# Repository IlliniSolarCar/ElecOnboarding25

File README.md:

# ElecOnboarding26
This is used for Electrical Onboarding for the Fall 2026 Semester

We are very excited to get to work with you guys!

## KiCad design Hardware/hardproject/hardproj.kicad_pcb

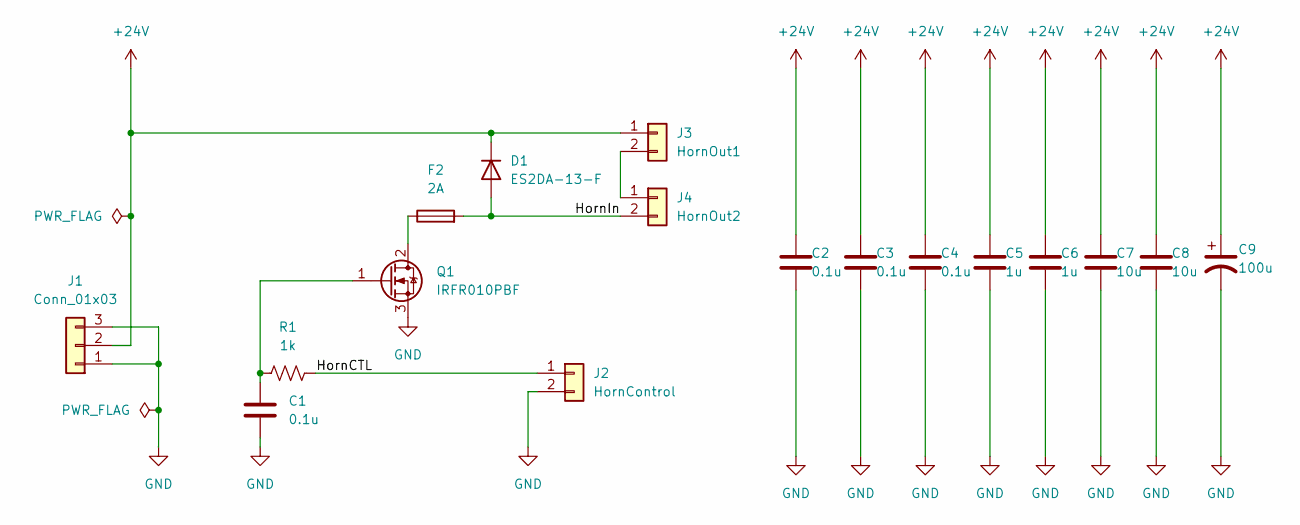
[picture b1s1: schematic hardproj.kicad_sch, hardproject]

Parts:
C1, C2, C3, C4: 0.1u; C_0603_1608Metric_Pad1.08x0.95mm_HandSolder
C5, C6: 1u; C_0603_1608Metric_Pad1.08x0.95mm_HandSolder
C7, C8: 10u; C_0603_1608Metric_Pad1.08x0.95mm_HandSolder
C9: 100u; C_Radial_D8.0mm_H11.5mm_P3.50mm
D1: ES2DA-13-F; D_SMA; MPN ES2DA-13-F
F2: 2A; Fuse_0603_1608Metric_Pad1.05x0.95mm_HandSolder
J1: Conn_01x03; Molex_KK-254_AE-6410-03A_1x03_P2.54mm_Vertical; MPN 022272021
J2: HornControl; Molex_KK-254_AE-6410-02A_1x02_P2.54mm_Vertical; MPN 0022272021
J3: HornOut1; Molex_KK-254_AE-6410-02A_1x02_P2.54mm_Vertical; MPN 0022272021
J4: HornOut2; Molex_KK-254_AE-6410-02A_1x02_P2.54mm_Vertical; MPN 0022272021
Q1: IRFR010PBF; TO-252-2; MPN IRFR010PBF
R1: 1k; R_0603_1608Metric_Pad0.98x0.95mm_HandSolder

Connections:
+24V: C2.1, C3.1, C4.1, C5.1, C6.1, C7.1, C8.1, C9.1, D1.1 (K), J1.2, J3.1
/HornCTL: J2.1, R1.2
/HornIn: D1.2 (A), F2.2, J4.2
GND: C1.2, C2.2, C3.2, C4.2, C5.2, C6.2, C7.2, C8.2, C9.2, J1.1, J1.3, J2.2, Q1.3 (S)
unnamed: J3.2, J4.1
unnamed: F2.1, Q1.2 (D)
unnamed: C1.1, Q1.1 (G), R1.1

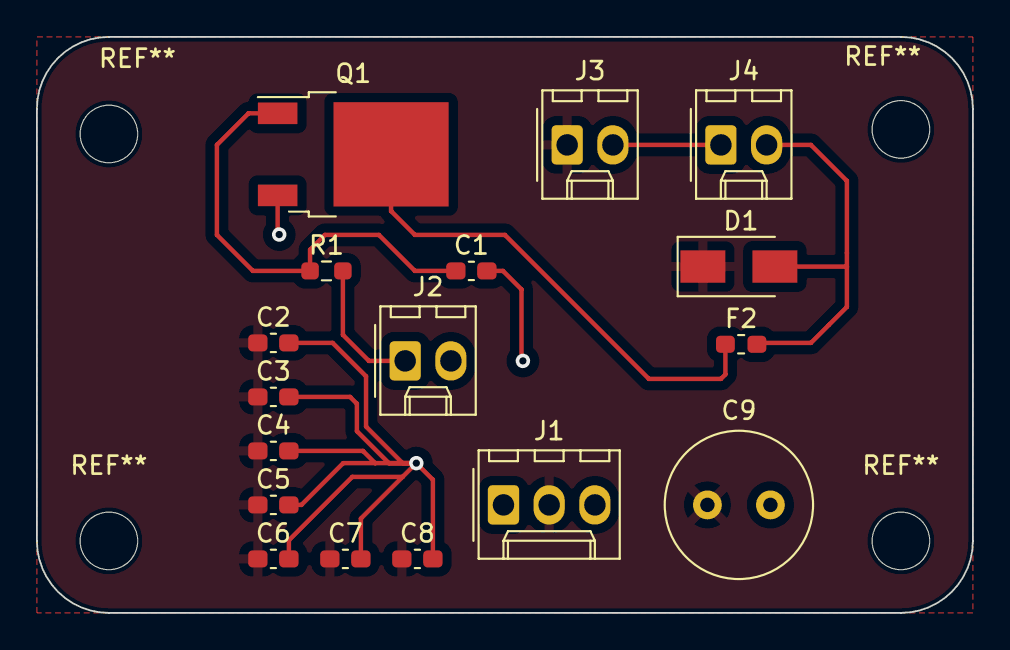
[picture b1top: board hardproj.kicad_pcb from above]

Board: 2 copper layers, 52.0 x 32.0 mm, 17 parts (0 on the bottom side), 7 nets.

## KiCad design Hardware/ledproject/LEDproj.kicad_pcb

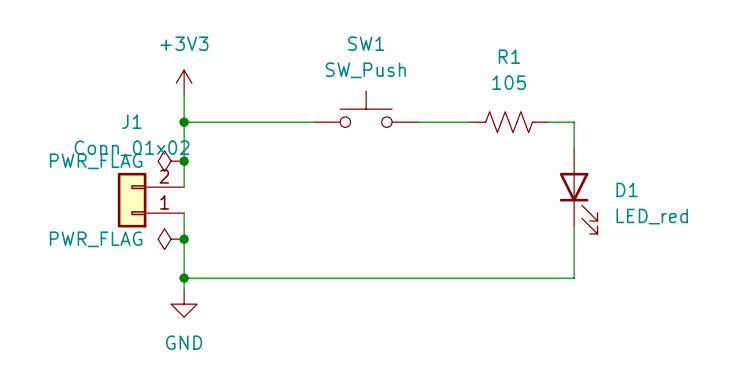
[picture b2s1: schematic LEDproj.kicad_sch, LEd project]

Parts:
D1: LED_red; LED_0603_Symbol_on_F.SilkS
J1: Conn_01x02; Molex_KK-254_AE-6410-02A_1x02_P2.54mm_Vertical; MPN 022272021
R1: 105; R_0603_1608Metric_Pad0.98x0.95mm_HandSolder
SW1: SW_Push; SW_DIP_SPSTx01_Slide_6.7x4.1mm_W8.61mm_P2.54mm_LowProfile; MPN 1825910-6

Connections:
+3V3: J1.2, SW1.1
GND: D1.1 (K), J1.1
unnamed: D1.2 (A), R1.1
unnamed: R1.2, SW1.2

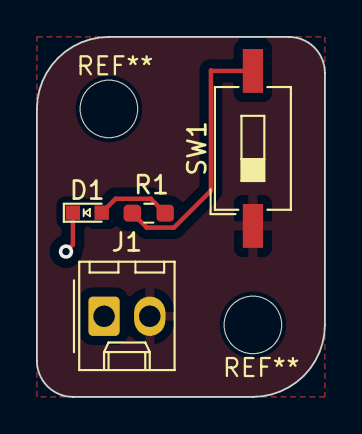
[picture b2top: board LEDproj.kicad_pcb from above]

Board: 2 copper layers, 16.0 x 20.0 mm, 4 parts (0 on the bottom side), 4 nets.

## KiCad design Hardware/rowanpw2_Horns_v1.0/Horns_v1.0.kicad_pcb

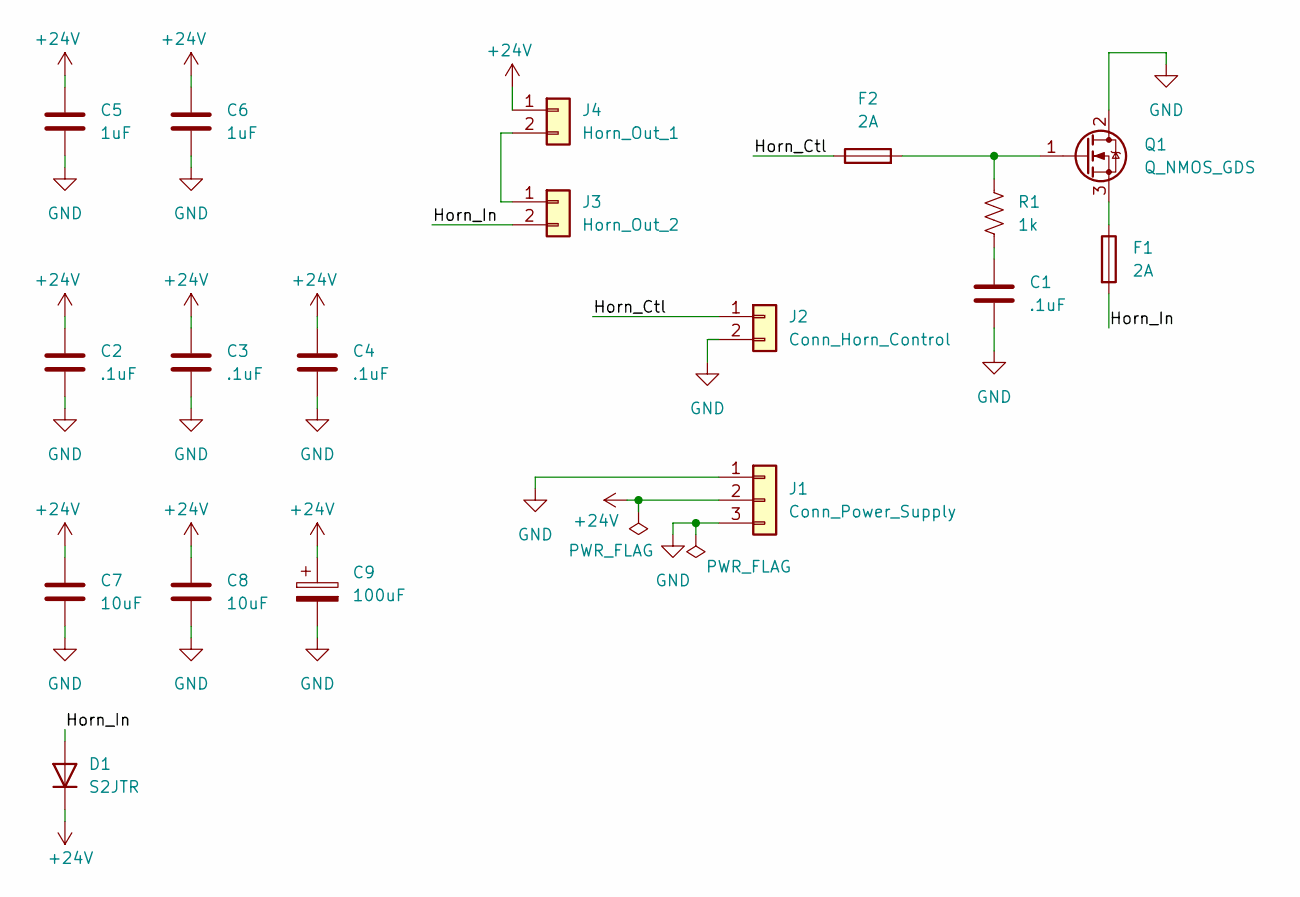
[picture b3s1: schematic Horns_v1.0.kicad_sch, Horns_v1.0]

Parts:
C1, C2, C3, C4: .1uF; C_0603_1608Metric_Pad1.08x0.95mm_HandSolder
C5, C6: 1uF; C_0603_1608Metric_Pad1.08x0.95mm_HandSolder
C7, C8: 10uF; C_0603_1608Metric_Pad1.08x0.95mm_HandSolder
C9: 100uF; CP_Elec_8x10; MPN UCM1A102MNS1GS
D1: S2JTR; D_SMB; MPN S2JTR
F1, F2: 2A; Fuse_1206_3216Metric_Pad1.42x1.75mm_HandSolder
J1: Conn_Power_Supply; Molex_KK-254_AE-6410-03A_1x03_P2.54mm_Vertical; MPN 0022272031
J2: Conn_Horn_Control; Molex_KK-254_AE-6410-02A_1x02_P2.54mm_Vertical; MPN 0022272021
J3: Horn_Out_2; Molex_KK-254_AE-6410-02A_1x02_P2.54mm_Vertical; MPN 0022272021
J4: Horn_Out_1; Molex_KK-254_AE-6410-02A_1x02_P2.54mm_Vertical; MPN 0022272021
Q1: Q_NMOS_GDS; TO-252-2; MPN AUIRF4905S
R1: 1k; R_0603_1608Metric_Pad0.98x0.95mm_HandSolder

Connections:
+24V: C2.1, C3.1, C4.1, C5.1, C6.1, C7.1, C8.1, C9.1, D1.1 (K), J1.2, J4.1
/Horn_Ctl: F2.1, J2.1
/Horn_In: D1.2 (A), F1.2, J3.2
GND: C1.2, C2.2, C3.2, C4.2, C5.2, C6.2, C7.2, C8.2, C9.2, J1.1, J1.3, J2.2, Q1.2 (D)
unnamed: C1.1, R1.2
unnamed: J3.1, J4.2
unnamed: F2.2, Q1.1 (G), R1.1
unnamed: F1.1, Q1.3 (S)

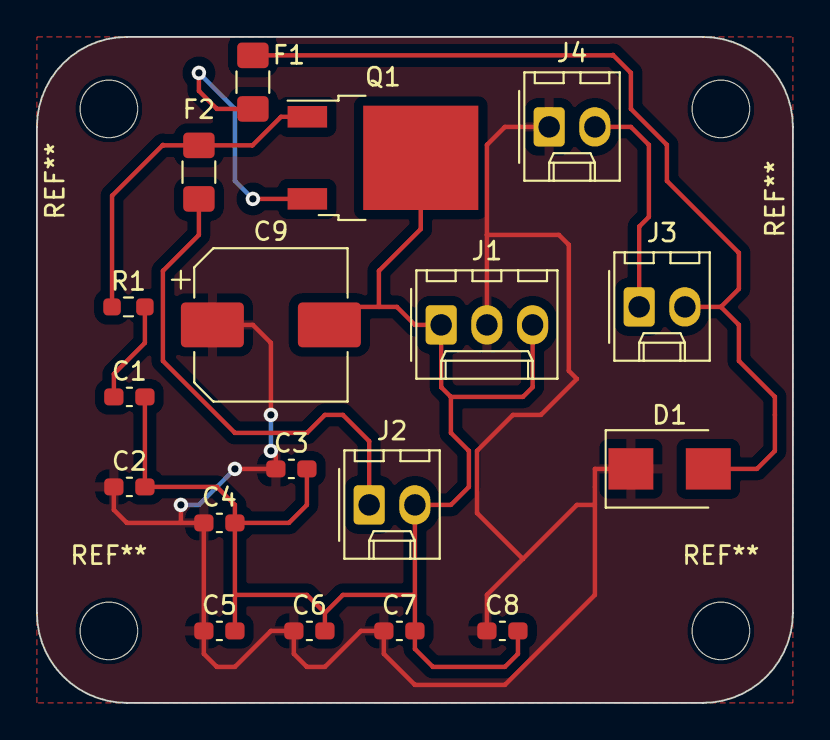
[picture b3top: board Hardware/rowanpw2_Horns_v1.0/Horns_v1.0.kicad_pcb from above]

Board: 2 copper layers, 42.0 x 37.0 mm, 18 parts (0 on the bottom side), 8 nets.

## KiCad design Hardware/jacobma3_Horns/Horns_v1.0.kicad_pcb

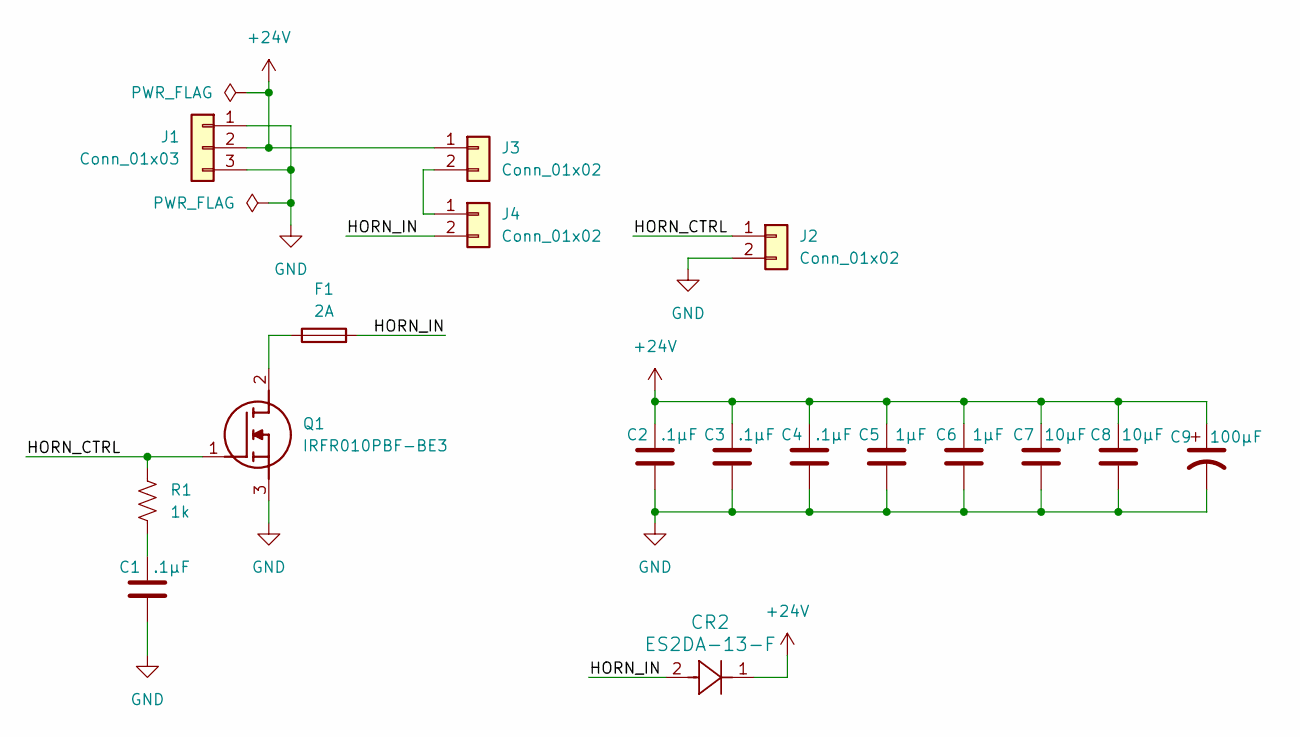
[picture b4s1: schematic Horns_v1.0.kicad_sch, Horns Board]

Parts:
C1, C2, C3, C4: .1μF; C_0603_1608Metric_Pad1.08x0.95mm_HandSolder
C5, C6: 1μF; C_0603_1608Metric_Pad1.08x0.95mm_HandSolder
C7, C8: 10μF; C_0603_1608Metric_Pad1.08x0.95mm_HandSolder
C9: 100μF; C_0603_1608Metric_Pad1.08x0.95mm_HandSolder
CR2: ES2DA-13-F; CR_SMA_DIO
F1: 2A; Fuse_0603_1608Metric_Pad1.05x0.95mm_HandSolder
J1: Conn_01x03; Molex_CLIK-Mate_502382-0370_1x03-1MP_P1.25mm_Vertical
J2, J3, J4: Conn_01x02; Molex_CLIK-Mate_502382-0270_1x02-1MP_P1.25mm_Vertical
Q1: IRFR010PBF-BE3; SQD30N0520L_GE3; Manufacturer_Part_Number IRFR010PBF-BE3; Mouser Part Number 78-IRFR010PBF-BE3
R1: 1k; R_0402_1005Metric_Pad0.72x0.64mm_HandSolder

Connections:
+24V: C2.2, C3.2, C4.2, C5.2, C6.2, C7.2, C8.2, C9.1, CR2.1, J1.2, J3.1
/HORN_CTRL: J2.1, Q1.1 (G), R1.2
/HORN_IN: CR2.2, F1.2, J4.2
GND: C1.1, C2.1, C3.1, C4.1, C5.1, C6.1, C7.1, C8.1, C9.2, J1.1, J1.3, J2.2, Q1.3 (S)
unnamed: C1.2, R1.1
unnamed: J3.2, J4.1
unnamed: F1.1, Q1.2 (D)

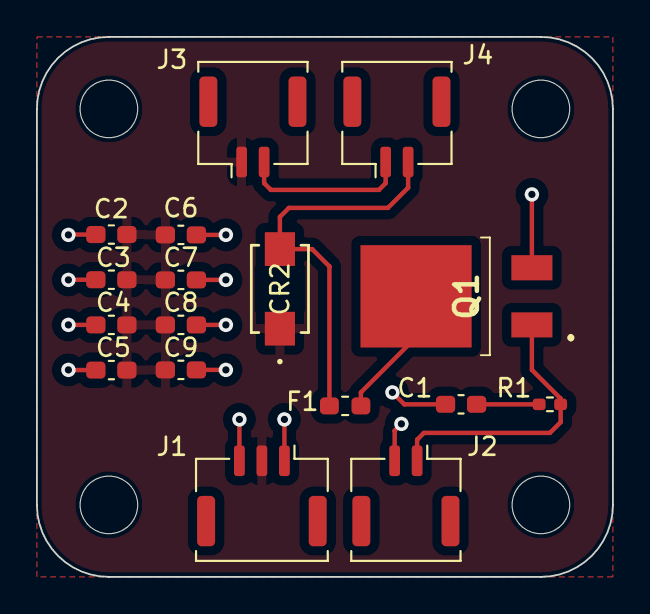
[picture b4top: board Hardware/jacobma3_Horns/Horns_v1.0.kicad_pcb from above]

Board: 2 copper layers, 32.0 x 30.0 mm, 17 parts (0 on the bottom side), 7 nets.

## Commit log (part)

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2025-09-19 Finished Horns Board Layout
    Fixed half-first order RC filter on MOSFET, finished PCB layout. Ran DRC with no errors.
2025-09-19 Finished hardware project 1
2025-09-19 Hardware project1 led pushbutton
2025-09-19 prog1
2025-09-19 Finished LED board schematic and PCB layout
2025-09-19 LED project
2025-09-19 easy projects done
2025-09-19 PCB Layout for Horn Breakout Board Done.
    Created the PCB for the Horn Breakout Board.
2025-09-19 Finished Hard Software Project
    Finished hard software project with potentiometer and LED. Added two lines of code.
2025-09-19 Specs
2025-09-19 firmware project 1 and project 2
2025-09-19 Schematic Horns
2025-09-19 Onboarding Horns Board PCB design
2025-09-19 Gerber files
2025-09-19 Finsihed Schematic for Horn
2025-09-19 Schematic changes
2025-09-20 Spec Sheet
2025-09-20 neha C++ project complete
2025-09-22 horns schematic complete (footprints incomplete)
2025-09-22 finished horns
2025-09-22 Proj 1 done
2025-09-22 blink
2025-09-22 Project 2: Potentiometer Blink Rate
    Finished Project 2 of Firmware and fixed an issue from project 1 of not setting a particular LED high/low
2025-09-23 hengrun2 onboarding project update 2025.9.22 20:46
2025-09-23 hengrun2 onboarding project 2025.9.22 23:03
2025-09-23 Onboarding Project 1 has been completed
2025-09-23 completed firmware proj1 LED
2025-09-23 heartbeat project submission
2025-09-24 Done with firmware?
2025-09-24 projectOneLEDThing
2025-09-24 Finshed Horn onboarding project all flags resolved
2025-09-24 Horns schematic
2025-09-24 Firmware project 1 done
2025-09-24 Project?
2025-09-24 neha horns schematic complete
2025-09-25 horns pcb
2025-09-25 firmware/hardware mini projects done
2025-09-25 Onboarding Hardware Project 1
2025-09-25 onboarding project 1's
2025-09-25 [finished basic hardware project]
2025-09-25 Hardware Project Finished
2025-09-25 Potentiometer Blink Rate Project
2025-09-25 schematic project 1
2025-09-25 finished LED Project
2025-09-25 Finished Schematic
2025-09-25 Working on pcb
2025-09-25 working on layout
2025-09-26 please
2025-09-26 Onboarding Basic Projects
2025-09-26 firmware projects
2025-09-26 Horns Spec Sheet
2025-09-26 testing the push
2025-09-26 Add Firmware easy project
2025-09-26 Onboarding Firmware Project 1
2025-09-26 Added firmware project
2025-09-26 Basic Firmware Project
    Completed basic firmware project.
2025-09-26 Advanced Hardware Project
    Completed schematic for advanced hardware project.
2025-09-26 Finish firmware mini. Start working on hardware mini
2025-09-26 submissions
2025-09-26 hardware mini & firmware mini done
2025-09-26 Heartbeat Firmware Project
2025-09-26 Firmware project 2 done?
2025-09-26 DFM Report
2025-09-26 HornsBoard Schematic
2025-09-26 Horns Board Schematic + footprint
2025-09-26 pushing spec sheet
2025-09-26 horns board
2025-09-26 prog2 is the working one
2025-09-26 Added prog2
2025-09-27 odom mom project 1 complete
2025-09-27 Potentiometer blink submission
2025-09-27 Finished layout
2025-09-27 LED Intro Project
2025-09-27 Horns Board PCB
2025-09-27 firmware hearbeat project
2025-09-27 LED Blinking Project 1&2
2025-09-27 pcb layout done
2025-09-27 gerber files and instant dfm added, lowkey I think they are incredibly wrong but I have no idea what to do about that and its late
2025-09-27 Horns Board (Challenge) Project
    Board to control the horns on the car. Includes schematic, layout, and specifications sheet.
2025-09-27 Horns Board + gbr files
    Added .zip folder of gbr files.
2025-09-27 Update horns_board.kicad_pcb
    Additional changes arising from the DFM setup.
2025-09-27 Project 2 spec sheet
2025-09-27 Project 1 (Hardware)
2025-09-27 project 2 - completed but most likely not working
2025-09-28 Completed introductory firmware project
    This adds one LED (myLED or led_5), and turns it on and off at 1 Hz.
2025-09-28 pushing horn schematic
2025-09-28 Did 1st project, error on DRC due to manufactured part violating clearance rule, otherwise good
2025-09-28 pushing pcb
2025-09-28 Specs sheet for horns is done
2025-09-28 Specs Sheet updating
2025-09-28 Hardware onboarding LED project
2025-09-28 Add Horns board specs and schematic
2025-09-28 LED Blinking Project Complete
2025-09-28 Completed Project 2 (Firmware); just pushed project wrong at first.
2025-09-28 completed basic firmware project, just pushed wrong initially.
2025-09-28 Finished the first firmware project.
2025-09-29 heartbeat
2025-09-29 Finished project 1 (LED tutorial)
2025-09-29 Firmware Easy Project Completed
2025-09-29 Firmware Project 1 Completed Code
2025-09-29 LED v1.0 schematic
2025-09-29 finished the first (baseline) and second (challenge) firmware projects
2025-09-29 LED Onboarding Project
    I have finished my LED Project and want some feedback
2025-09-29 Antonio Project 1 Finish
2025-09-29 potentiometer blink rate
2025-09-29 kevinz16 Onboarding: Hard hardware project
2025-09-29 mini projects and advanced firmware project completed
2025-09-30 Firmware_1
2025-09-30 jwang849 firmware project 1 complete
2025-09-30 Your message here
2025-09-30 Hardware project 1 completed
2025-09-30 Onboarding
2025-09-30 Specs file
2025-09-30 Add heartbeat LED logic
2025-09-30 firmware project 1
2025-09-30 Heartbeat Project Complete
2025-09-30 Sure hope this works
2025-09-30 hardware part 1
2025-09-30 firmware project 2 complete
2025-09-30 jwang849 firmware project 2 completed
2025-09-30 implemented changes to board and code
2025-09-30 adding Hardware mini project
2025-09-30 feat: project1 hardware led circuit
2025-09-30 feat: project1 firmware heartbeat
2025-10-01 fixed silkscreen for hardware
2025-10-01 Challenged Hardware Project
2025-10-01 iandoll2 horn project complete
2025-10-01 Quinn Zhang LED Onboarding Project 1
2025-10-01 Kicad and MCUXpresso changes
2025-10-01 reuploading LED project
2025-10-01 Create fp-lib-table
2025-10-01 LED Project Update
2025-10-01 Very Challenged Hardware
2025-10-01 completed firmware and hardware project 1
2025-10-01 fixed firmware #2
2025-10-01 Updated Connector Footprints
    Changed from KK254 to Molex Micro-Fit Connector footprints. Updated layout as well, passed DRC with no errors or warnings.
2025-10-01 jwang849 firmware project 2 second attempt
2025-10-01 firmware project 1 submit
2025-10-01 feat: project1 hardware
2025-10-01 fix footprints
2025-10-01 Updated User Drawings
    Forgot to change User Drawing dimensions when modifying layout to fit new footprints.
2025-10-01 Finished easy hardware project
2025-10-01 re-added unsaved changes
2025-10-01 pushing 2 mini projects and hardware challenge project
2025-10-01 submitting both firmare projects
2025-10-01 Add updates based on feedback
2025-10-01 firmware project 2
2025-10-01 horn_board_specs
2025-10-01 didnt do the gerber thingy bc no directions as tutorial is broken
2025-10-01 finished the schematic for the Horns project
2025-10-01 hardware project 2 schematic complete
2025-10-01 Project 1 (Hardware) Completed
2025-10-01 Project 2 (Firmware) Added missing file
2025-10-01 firmware project1
2025-10-01 Updated according to comments
    Split schematic into multiple modules instead of a single loop.
    Replaced Molex kk254 connectors with micro fit and rerouted the traces accordingly.
2025-10-01 Very Challenged Circuits
2025-10-01 LED circuit
2025-10-01 Updated hardware onboarding project files
2025-10-01 added hardware
2025-10-02 schematic1
2025-10-02 Minor adjustments to the wiring on the horns board
2025-10-02 fixed things related to horns such as changing connectors, removing the switch, and removing power planes as well as general rerouting of everything
2025-10-02 integrated feedback
2025-10-02 Horn Board Spec Sheet
2025-10-02 Complete Firmwware Project 1
2025-10-02 update 10/1
2025-10-02 Delcare ratepot in pins.h
2025-10-02 Added completed project 1 files
2025-10-02 placeholder file to make folder dw about it
2025-10-02 Adding finished project 1 files to correct folder
2025-10-02 Instantiate ratepot with P_RATEPOT in pins.cpp
2025-10-02 Fix firmware project 1 to correct write 0/1
2025-10-02 Horns Board schematic
2025-10-02 Complete project 2
2025-10-02 Redefine P_RATEPOT as pin A0_1 as it is analog
2025-10-02 Update pins.cpp for proj 2
2025-10-02 Update main.cpp for proj 2
2025-10-02 Finished LED Project 1
2025-10-02 Ethan Regirer Project 1
2025-10-02 firmware error fix and changed hardware connector footprints
2025-10-02 Firmware Proj 1 & Horns Schematic
2025-10-02 Horns PCB with correct connector
2025-10-02 Project 1 firmware
2025-10-02 Completion of firmware heartbeat
2025-10-02 fix: POT blink var name bug
2025-10-02 projects
2025-10-02 update pcb layout
2025-10-02 Horns Project Finish
2025-10-03 Rready to push
2025-10-03 final push
2025-10-03 completed led project
2025-10-03 Should be done with Horn's project
2025-10-03 Added corrected pins.cpp file
2025-10-03 WIP: heartbeat project – added LED toggle logic in main.cpp
2025-10-03 Redo diode
2025-10-03 fixed basic coding project
2025-10-03 fixed erc errors for horns
2025-10-03 Finish easy firmware project
2025-10-03 hardware project 2 horn board submit
2025-10-03 Fixed includes and toggleLed function
2025-10-03 LEDPROJECTDONE
2025-10-03 specs filled out
2025-10-03 gerber files for my circuit
2025-10-03 I have tried my hardest and at this point my circuit looks ok, everything definitely isn't perfect
2025-10-03 Commiting my entire Firmware folder which has everything updated
2025-10-03 corrections made to Horns/LED
2025-10-03 Onboarding Check FIX
    Switched the connector footprints, and rearranged the rectifier diode to protect against current back flow and from high current flowing through the mosfet/tripping the fuse. Re-arranged the PCB layo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
2025-10-03 Final Onboarding Project Submission CHECK ONBOARDING FOLDER
2025-10-03 Finished project 2, working poetentiometer
2025-10-03 Finished basic firmware onboarding project, starting advanced hardware project
2025-10-04 added gerber files and finished horns board
2025-10-04 files did not appear last commit
2025-10-04 firmwareproject1
2025-10-04 Pushing both basic onboarding projects and advanced hardware project.
2025-10-04 firmware
2025-10-04 finsihed?????
2025-10-04 corrected firmware project1 and completion of firmware project2(challenge)
2025-10-04 adding Hardware 2 project
2025-10-04 Finished horns schematic
2025-10-04 ERC and DRC checks (passed)
2025-10-04 updated footprints for connectors in schematic
2025-10-04 Firmware project done to the best of my ability
2025-10-04 Onboarding firmware easy&challenge projects
2025-10-04 schematic
2025-10-04 finished project 2 for firmware
2025-10-04 Pushing Spec Sheet and Schematic
2025-10-04 finished horn schematic
2025-10-04 fixed hornsboard
2025-10-04 Firmware Hard Project Completed
2025-10-04 finished horn PCB
2025-10-04 Hardware Project_2
2025-10-04 Firmware Hard Proj Revisions
2025-10-05 Ethan Regirer project 2 schematic
2025-10-05 add prog1
2025-10-05 onboarding projects
2025-10-05 onboarding easy projects update
2025-10-05 All of onboarding complete!
2025-10-05 Submitting attempt at Horns
2025-10-05 horns board complete + dfm
2025-10-05 Add prog2 project and update files
2025-10-05 Hardware Project 2
2025-10-05 finished hardware project (Easy + Challenge); still waiting for the DFM report)
2025-10-05 Updated Horns Board schematic, PCB design, and gerber files
2025-10-05 Onboarding Complete!
2025-10-05 I finished firmware project 1, hardware project 1, and the horn challenge. They are in the onboarding projects folder.
2025-10-05 These are the files for my projects :]
2025-10-05 finished firmware (easy)
2025-10-05 finished finished
2025-10-05 horns board v1 done, only look at v1.0
2025-10-05 updated folder name
2025-10-05 2nd project push
2025-10-05 Fixed error of misplaced semi-colon on pins.cpp, made best attempt at Firmware Challenge Project. Did best to clean up Firmware Introduction Project 1.
2025-10-05 Firmware #2 Potentiometer
2025-10-05 Finished firmware 2
2025-10-05 gerbers
2025-10-05 Horns Board Project: Incomplete
2025-10-05 Prog5 is redone firmware easy project
2025-10-05 Redone firmware challenge project
2025-10-05 ALL DONE!
2025-10-05 Forgot firmware files!
2025-10-05 Horns project PCB complete
2025-10-05 Horns Board Project
2025-10-05 Horns pcb completed
2025-10-05 Firmware Challenge (Potentiometer)
2025-10-06 implemented feedback
2025-10-06 Applied changes to the diode
